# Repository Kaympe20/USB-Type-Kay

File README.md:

# USB Type-Kay

<br>

A USB-A Hub powered by USB-C.

I made this powered USB Hub because I use a USB Hub at my desk, but not everything works correctly when it doesn't recieve all of the 500mA current. It would be much nicer if there was enough power such that each port could have the full power of a regular USB-A port.

## Pics

## CAD

The entire CAD workspace can be found on [Onshape](https://cad.onshape.com/documents/c7f694b62a224799f4cb962e/w/0d1c46c09d0047ca434a2fd4/e/c17be9d34015dc597f20f24c?renderMode=0&uiState=688c152b25b23a519670e553)

## BOM

| Item | Quantity | Price | Price After Taxes + Shipping |
|------|----------|-------|------------------------------|
[Assembled PCB](https://github.com/Kaympe20/USB-Type-Kay/tree/main/production) | 1 | $28.01 | $80.56
[3D Printed Case](https://github.com/Kaympe20/Kaypaw96/blob/main/cad/Case.step) | 1 | $0 | $0
[M2 Hardware](https://www.amazon.com/QOOSIKICC-Assortment-Washers-Machine-Assorted/dp/B0DDY2L533) | N/a | $6.99 | $7.41
[M1 Hardware](https://www.amazon.com/Stainless-Assortment-Fasteners-Repairing-Electronics/dp/B09MS6KPN7) | N/a | $5.29 | $5.61

Total: $93.58

Here's the parts I selected in JLCPCB

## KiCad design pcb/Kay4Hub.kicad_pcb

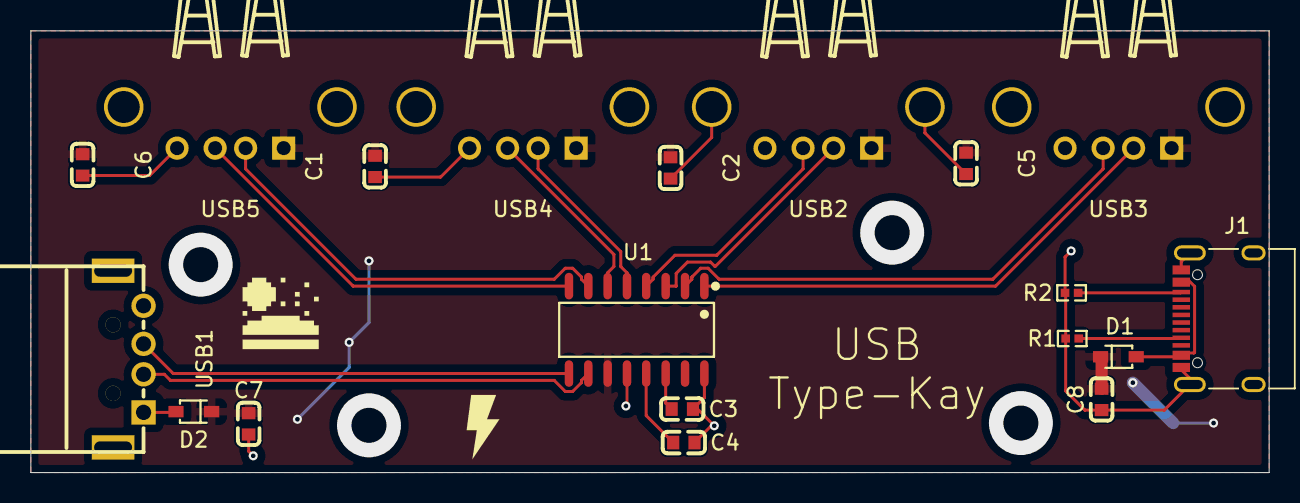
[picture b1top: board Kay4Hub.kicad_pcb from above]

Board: 2 copper layers, 81.3 x 29.0 mm, 19 parts (0 on the bottom side), 18 nets.

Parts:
C1, C2, C3, C4, C5, C6, C7, C8: 10uF; C0603
D1, D2: D; SOD-323_L1.8-W1.3-LS2.5-RD
J1: USB_C_Receptacle_USB2.0_14P; USB_C_Receptacle_XKB_U262-16XN-4BVC11
R1, R2: 5.1k; R0402
U1: SL2.1A; SOP-16_L10.0-W3.9-P1.27-LS6.0-BL
USB1: U-G-04DD-W-01; USB-A-TH_U-G-04WD-W-01
USB2, USB3, USB4, USB5: USB-AF-90-14.4X13.6-H7.0-DIP; USB-A-TH_C46407

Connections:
1D+: U1.8 (DP1), USB5.3 (D+)
1D-: U1.7 (DM1), USB5.2 (D-)
2D+: U1.6 (DP2), USB4.3 (D+)
2D-: U1.5 (DM2), USB4.2 (D-)
3D+: U1.4 (DP3), USB2.3 (D+)
3D-: U1.3 (DM3), USB2.2 (D-)
4D+: U1.2 (DP4), USB3.3 (D+)
4D-: U1.1 (DM4), USB3.2 (D-)
+5V: C1.2, C2.1, C5.1, C6.1, C7.1, C8.2, D1.1 (K), D2.1 (K), U1.11 (VDD5), USB2.1 (VCC), USB3.1 (VCC), USB4.1 (VCC), USB5.1 (VCC)
D+: U1.10 (DP), USB1.2 (D-)
D-: U1.9 (DM), USB1.3 (D+)
GND: C1.1, C2.2, C3.2, C4.2, C5.2, C6.2, C7.2, C8.1, J1.A1 (GND), J1.A12 (GND), J1.B1 (GND), J1.B12 (GND), J1.S1 (SHIELD), R1.2, R2.2, U1.12 (GND), U1.16 (XIN), USB1.4 (GND), USB1.5, USB1.6, USB2.4 (GND), USB2.5, USB2.6, USB3.4 (GND), USB3.5, USB3.6, USB4.4 (GND), USB4.5, USB4.6, USB5.4 (GND), USB5.5, USB5.6
unnamed: D1.2 (A), J1.A4 (VBUS), J1.A9 (VBUS), J1.B4 (VBUS), J1.B9 (VBUS)
unnamed: D2.2 (A), USB1.1 (VCC)
unnamed: J1.A5 (CC1), R1.1
unnamed: J1.B5 (CC2), R2.1
unnamed: C3.1, U1.14 (VDD18)
unnamed: C4.1, U1.13 (VDD33)

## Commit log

2025-07-31 Finish PCB
2025-08-01 Add all changes needed for Highway Submission
2025-08-04 Update design with more stuff
2025-08-06 Connect those pins
2025-08-06 Add last entry
